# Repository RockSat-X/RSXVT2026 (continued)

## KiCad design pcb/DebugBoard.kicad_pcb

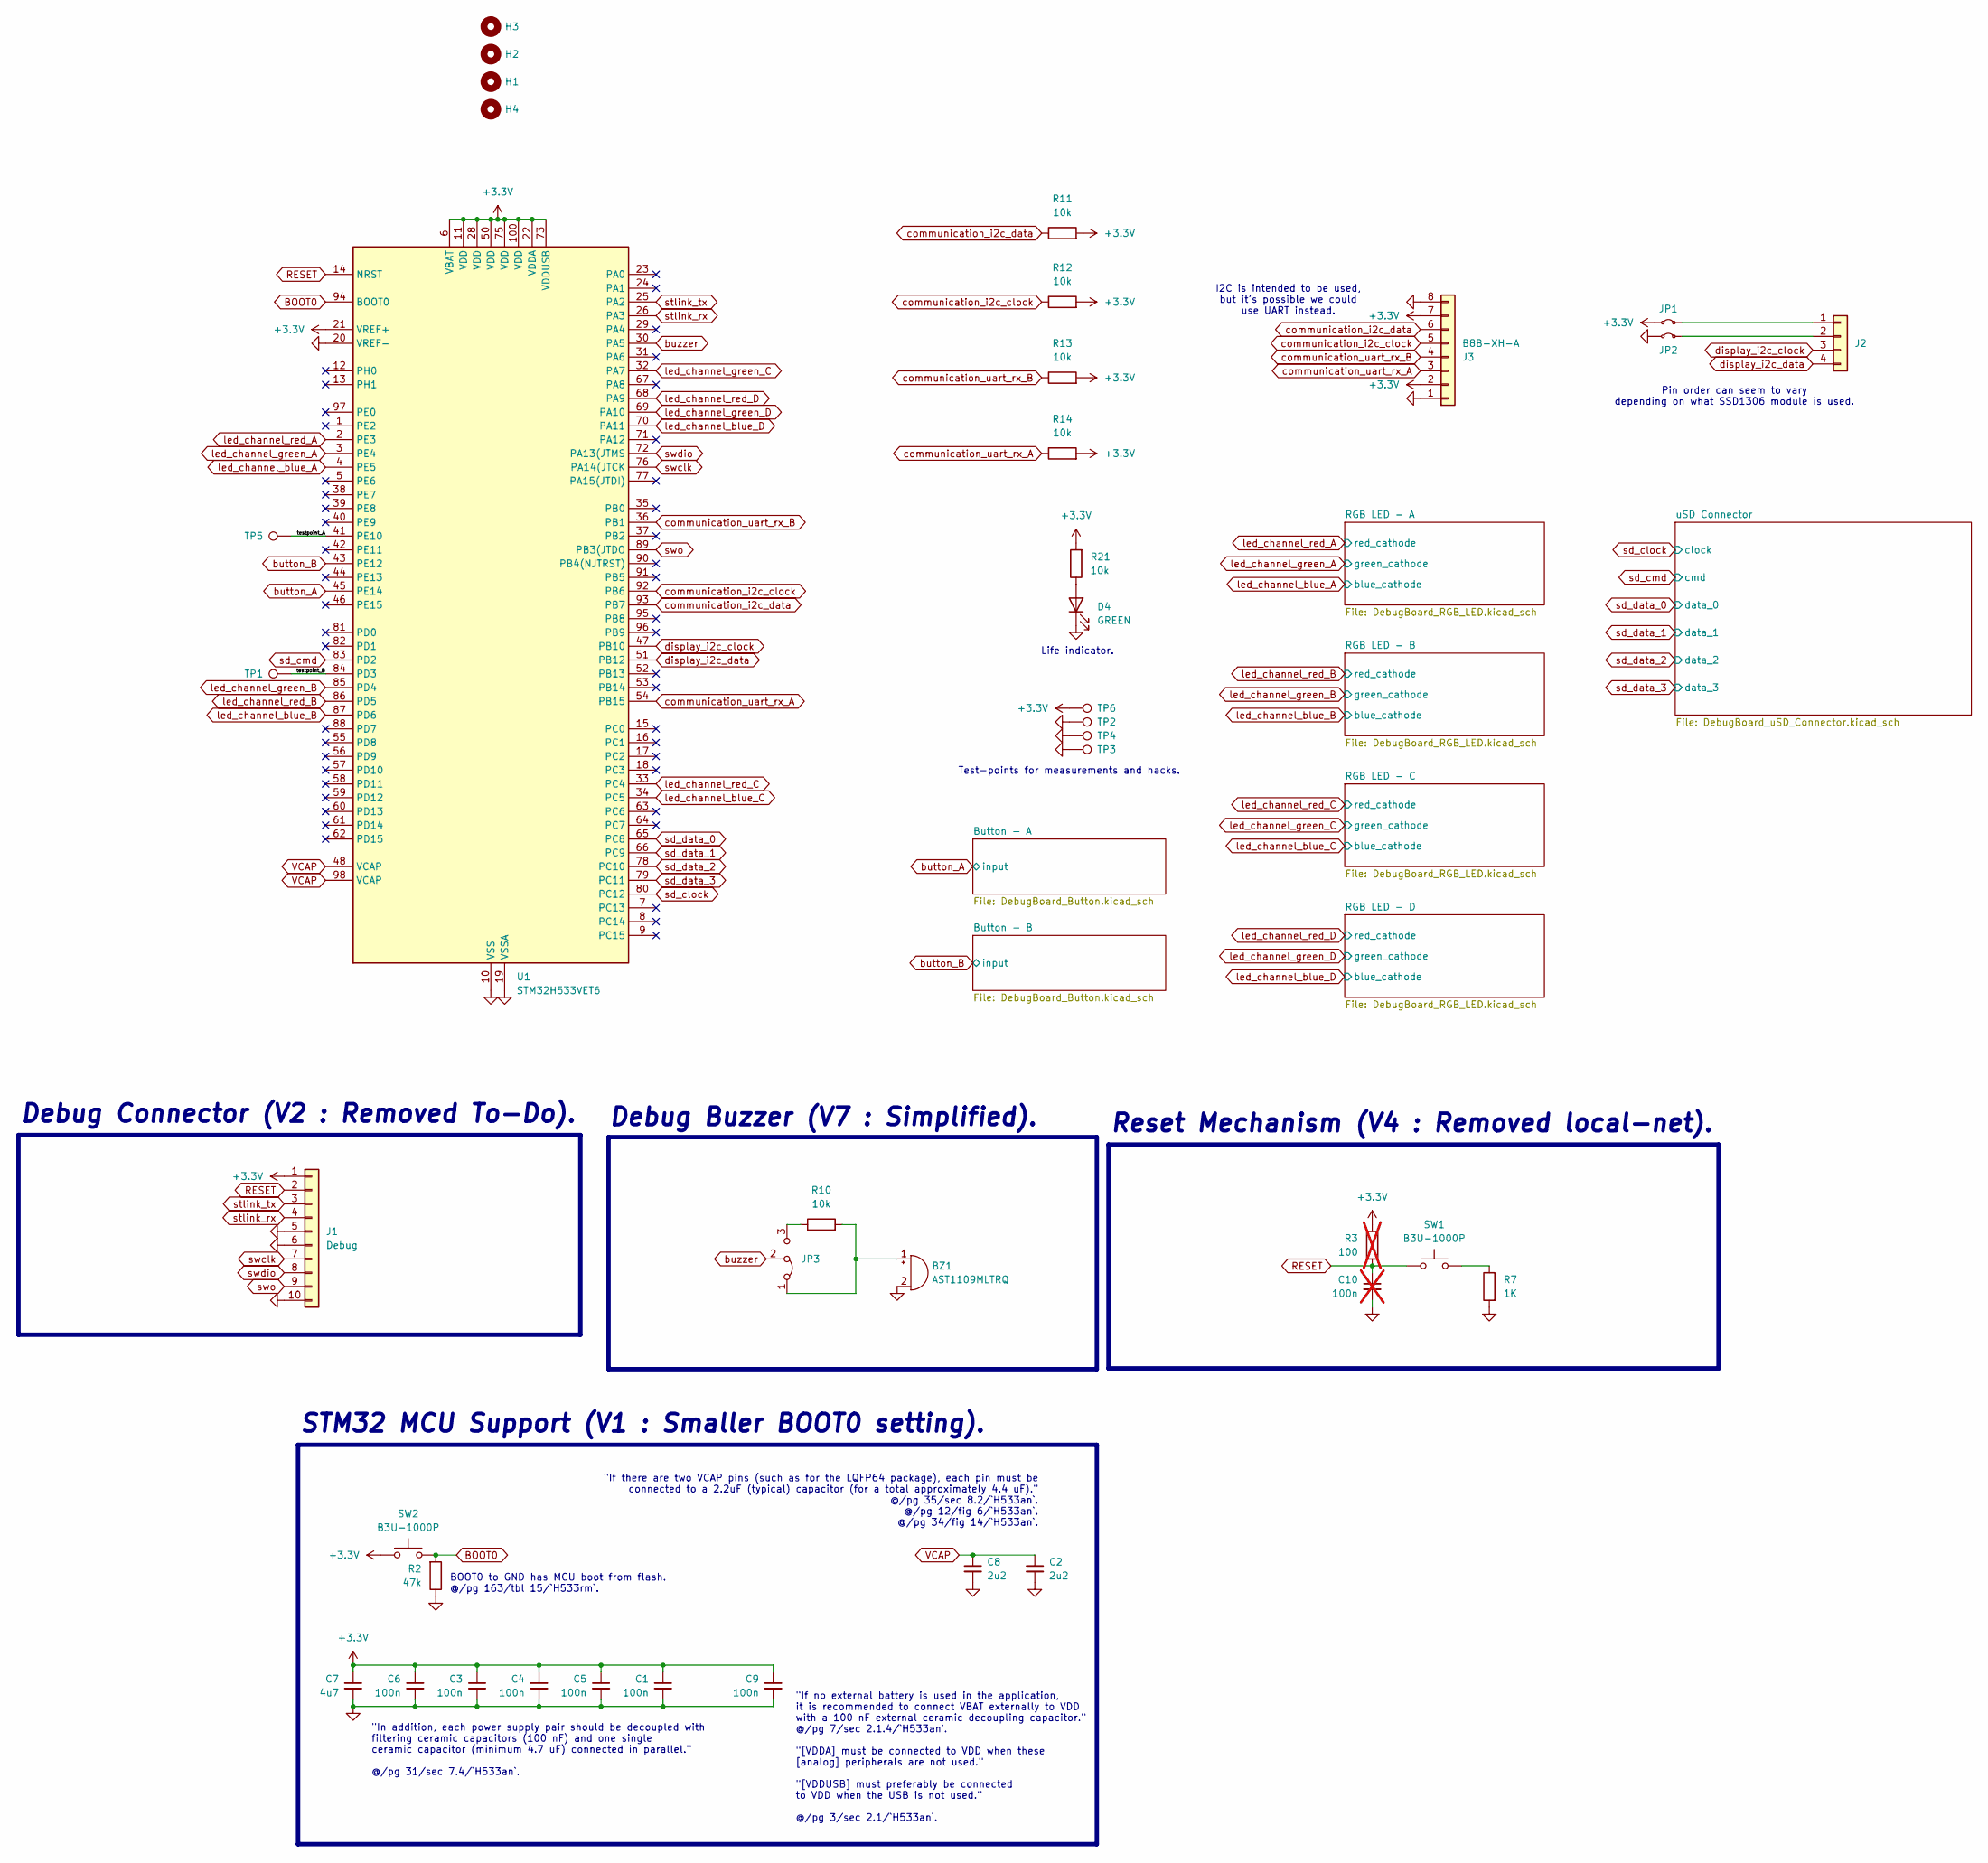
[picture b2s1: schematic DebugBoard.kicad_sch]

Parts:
BZ1: AST1109MLTRQ; Buzzer_Mallory_AST1109MLTRQ
C1, C3, C4, C5, C6, C9: 100n; C_1206_3216Metric_Pad1.33x1.80mm_HandSolder
C2, C8: 2u2; C_1206_3216Metric_Pad1.33x1.80mm_HandSolder
C7: 4u7; C_1206_3216Metric_Pad1.33x1.80mm_HandSolder
C10: 100n; C_1206_3216Metric_Pad1.33x1.80mm_HandSolder; not fitted
D4: GREEN; LED_1206_3216Metric_Pad1.42x1.75mm_HandSolder
H1, H2, H3, H4: MountingHole; MountingHole_3.2mm_M3
J1: Debug; Molex_PicoBlade_53047-1010_1x10_P1.25mm_Vertical
J2: Conn_01x04; SSD1306_Module_Connector
J3: B8B-XH-A; JST_XH_B8B-XH-A_1x08_P2.50mm_Vertical
JP1, JP2: Jumper_2_Small_Bridged; TestPoint_2Pads_Pitch2.54mm_Drill0.8mm
JP3: Jumper_3_Bridged12; PinHeader_1x03_P2.54mm_Vertical
R2: 47k; R_1206_3216Metric_Pad1.30x1.75mm_HandSolder
R3: 100; R_1206_3216Metric_Pad1.30x1.75mm_HandSolder; not fitted
R7: 1K; R_1206_3216Metric_Pad1.30x1.75mm_HandSolder
R10, R11, R12, R13, R14, R21: 10k; R_1206_3216Metric_Pad1.30x1.75mm_HandSolder
SW1, SW2: B3U-1000P; SW_SPST_B3U-1000P
TP1, TP2, TP3, TP4, TP5, TP6: TestPoint; TestPoint_Bridge_Pitch2.0mm_Drill0.7mm
U1: STM32H533VET6; LQFP-100_14x14mm_P0.5mm

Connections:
+3.3V: C1.1, C3.1, C4.1, C5.1, C6.1, C7.1, C9.1, J1.1, J3.2, J3.7, JP1.1 (A), R3.1, R11.2, R12.2, R13.2, R14.2, R21.2, SW2.1, TP6.1, U1.6 (VBAT), U1.11 (VDD), U1.21 (VREF+), U1.22 (VDDA), U1.28 (VDD), U1.50 (VDD), U1.73 (VDDUSB), U1.75 (VDD), U1.100 (VDD); also elsewhere on the board
/testpoint_A: TP5.1, U1.41 (PE10)
/testpoint_B: TP1.1, U1.84 (PD3)
BOOT0: R2.2, SW2.2, U1.94 (BOOT0)
GND: BZ1.2 (-), C1.2, C2.2, C3.2, C4.2, C5.2, C6.2, C7.2, C8.2, C9.2, C10.2, D4.1 (K), J1.5, J1.6, J1.10, J3.1, J3.8, JP2.1 (A), R2.1, R7.2, TP2.1, TP3.1, TP4.1, U1.10 (VSS), U1.19 (VSSA), U1.20 (VREF-), U1.27 (VSS), U1.49 (VSS), U1.74 (VSS), U1.99 (VSS); also elsewhere on the board
unnamed: BZ1.1 (+), JP3.1 (A), R10.2
unnamed: D4.2 (A), R21.1
unnamed: J2.1, JP1.2 (B)
unnamed: J2.2, JP2.2 (B)
unnamed: JP3.3 (B), R10.1
unnamed: R7.1, SW1.2
RESET: C10.1, J1.2, R3.2, SW1.1, U1.14 (NRST)
VCAP: C2.1, C8.1, U1.48 (VCAP), U1.98 (VCAP)
button_A: U1.45 (PE14); also elsewhere on the board
button_B: U1.43 (PE12); also elsewhere on the board
buzzer: JP3.2 (C), U1.30 (PA5)
communication_i2c_clock: J3.5, R12.1, U1.92 (PB6)
communication_i2c_data: J3.6, R11.1, U1.93 (PB7)
communication_uart_rx_A: J3.3, R14.1, U1.54 (PB15)
communication_uart_rx_B: J3.4, R13.1, U1.36 (PB1)
display_i2c_clock: J2.3, U1.47 (PB10)
display_i2c_data: J2.4, U1.51 (PB12)
led_channel_blue_A: U1.4 (PE5); also elsewhere on the board
led_channel_blue_B: U1.87 (PD6); also elsewhere on the board
led_channel_blue_C: U1.34 (PC5); also elsewhere on the board
led_channel_blue_D: U1.70 (PA11); also elsewhere on the board
led_channel_green_A: U1.3 (PE4); also elsewhere on the board
led_channel_green_B: U1.85 (PD4); also elsewhere on the board
led_channel_green_C: U1.32 (PA7); also elsewhere on the board
led_channel_green_D: U1.69 (PA10); also elsewhere on the board
led_channel_red_A: U1.2 (PE3); also elsewhere on the board
led_channel_red_B: U1.86 (PD5); also elsewhere on the board
led_channel_red_C: U1.33 (PC4); also elsewhere on the board
led_channel_red_D: U1.68 (PA9); also elsewhere on the board
sd_clock: U1.80 (PC12); also elsewhere on the board
sd_cmd: U1.83 (PD2); also elsewhere on the board
sd_data_0: U1.65 (PC8); also elsewhere on the board
sd_data_1: U1.66 (PC9); also elsewhere on the board
sd_data_2: U1.78 (PC10); also elsewhere on the board
sd_data_3: U1.79 (PC11); also elsewhere on the board
stlink_rx: J1.4, U1.26 (PA3)
stlink_tx: J1.3, U1.25 (PA2)
swclk: J1.7, U1.76 (PA14(JTCK)
swdio: J1.8, U1.72 (PA13(JTMS)
swo: J1.9, U1.89 (PB3(JTDO)

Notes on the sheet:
STM32 MCU Support (V1 : Smaller BOOT0 setting).
Pin order can seem to vary depending on what SSD1306 module is used.
I2C is intended to be used, but it's possible we could use UART instead.
Reset Mechanism (V4 : Removed local-net).
Debug Connector (V2 : Removed To-Do).
BOOT0 to GND has MCU boot from flash. @/pg 163/tbl 15/`H533rm`.
Life indicator.
Test-points for measurements and hacks.
"If there are two VCAP pins (such as for the LQFP64 package), each pin must be connected to a 2.2uF (typical) capacitor (for a total approximately 4.4 uF)." @/pg 35/sec 8.2/`H533an`. @/pg 12/fig 6/`H533an`. @/pg 34/fig 14/`H533an`.
"In addition, each power supply pair should be decoupled with filtering ceramic capacitors (100 nF) and one single ceramic capacitor (minimum 4.7 uF) connected in parallel." @/pg 31/sec 7.4/`H533an`.
"If no external battery is used in the application, it is recommended to connect VBAT externally to VDD with a 100 nF external ceramic decoupling capacitor." @/pg 7/sec 2.1.4/`H533an`. "[VDDA] must be connected to VDD when these [analog] peripherals are not used." "[VDDUSB] must preferably be conne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
Debug Buzzer (V7 : Simplified).

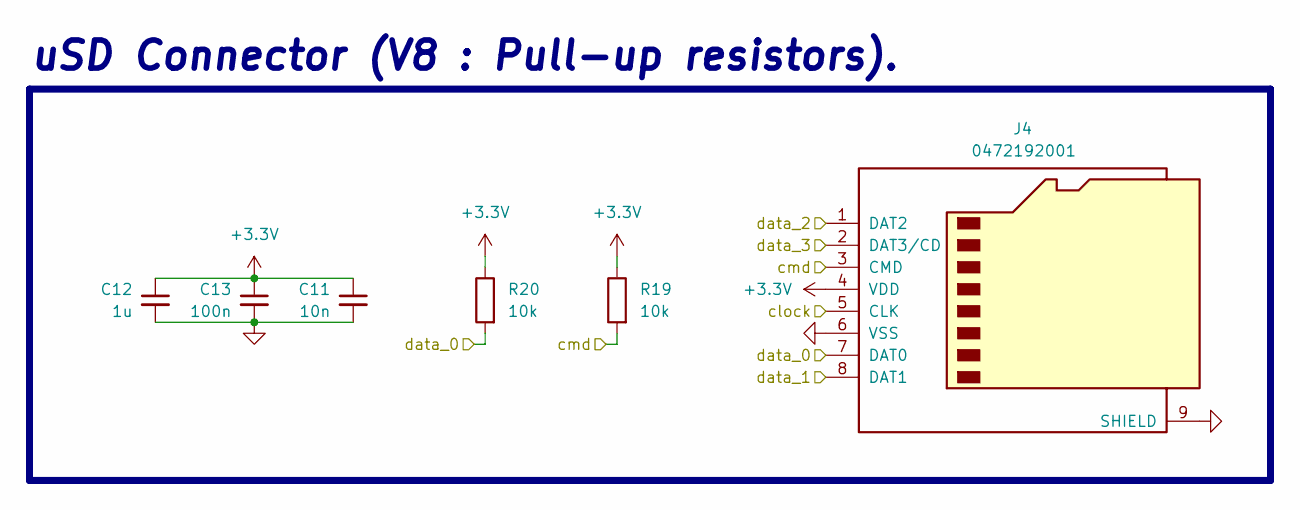
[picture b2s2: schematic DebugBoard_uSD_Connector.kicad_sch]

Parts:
C11: 10n; C_1206_3216Metric_Pad1.33x1.80mm_HandSolder
C12: 1u; C_1206_3216Metric_Pad1.33x1.80mm_HandSolder
C13: 100n; C_1206_3216Metric_Pad1.33x1.80mm_HandSolder
J4: 0472192001; microSD_HC_Molex_47219-2001
R19, R20: 10k; R_1206_3216Metric_Pad1.30x1.75mm_HandSolder

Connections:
+3.3V: C11.1, C12.1, C13.1, J4.4 (VDD), R19.1, R20.1; also elsewhere on the board
GND: C11.2, C12.2, C13.2, J4.6 (VSS), J4.9 (SHIELD); also elsewhere on the board
sd_clock: J4.5 (CLK); also elsewhere on the board
sd_cmd: J4.3 (CMD), R19.2; also elsewhere on the board
sd_data_0: J4.7 (DAT0), R20.2; also elsewhere on the board
sd_data_1: J4.8 (DAT1); also elsewhere on the board
sd_data_2: J4.1 (DAT2); also elsewhere on the board
sd_data_3: J4.2 (DAT3/CD); also elsewhere on the board

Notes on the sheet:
uSD Connector (V8 : Pull-up resistors).

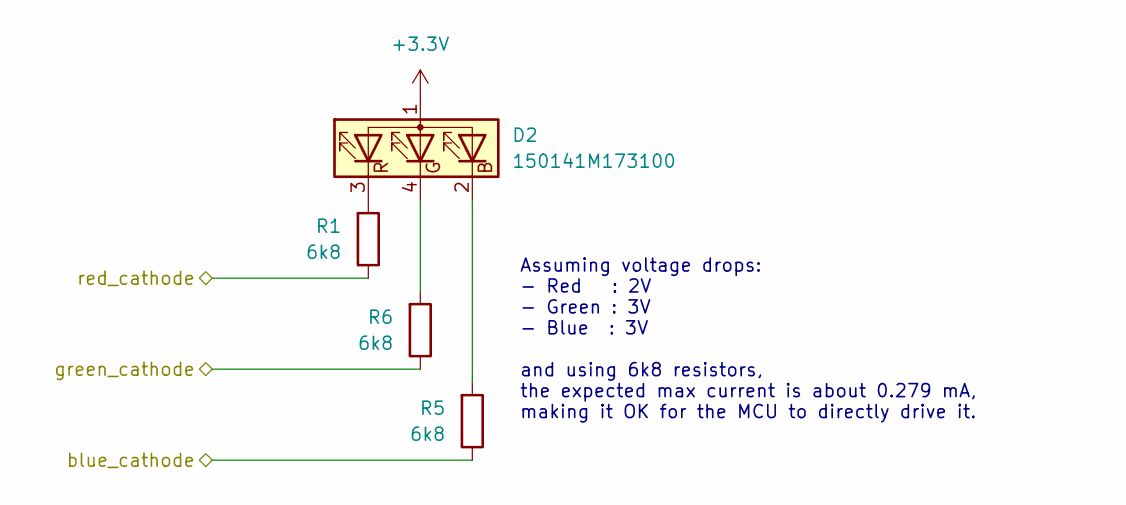
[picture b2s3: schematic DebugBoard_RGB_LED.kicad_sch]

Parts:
D2: 150141M173100; LED_RGB_Wuerth-PLCC4_3.2x2.8mm_150141M173100
R1, R5, R6: 6k8; R_1206_3216Metric_Pad1.30x1.75mm_HandSolder

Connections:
+3.3V: D2.1 (A); also elsewhere on the board
unnamed: D2.2 (BK), R5.2
unnamed: D2.4 (GK), R6.2
unnamed: D2.3 (RK), R1.2
led_channel_blue_A: R5.1; also elsewhere on the board
led_channel_green_A: R6.1; also elsewhere on the board
led_channel_red_A: R1.1; also elsewhere on the board

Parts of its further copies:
D1, D3, D5: 150141M173100; LED_RGB_Wuerth-PLCC4_3.2x2.8mm_150141M173100
R4, R8, R9, R17, R18, R22, R23, R24, R25: 6k8; R_1206_3216Metric_Pad1.30x1.75mm_HandSolder

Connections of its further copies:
+3.3V: D1.1 (A), D3.1 (A), D5.1 (A); also elsewhere on the board
unnamed: D1.2 (BK), R8.2
unnamed: D1.4 (GK), R9.2
unnamed: D1.3 (RK), R4.2
unnamed: D3.2 (BK), R22.2
unnamed: D3.4 (GK), R23.2
unnamed: D3.3 (RK), R25.2
unnamed: D5.2 (BK), R18.2
unnamed: D5.4 (GK), R17.2
unnamed: D5.3 (RK), R24.2
led_channel_blue_B: R8.1; also elsewhere on the board
led_channel_blue_C: R18.1; also elsewhere on the board
led_channel_blue_D: R22.1; also elsewhere on the board
led_channel_green_B: R9.1; also elsewhere on the board
led_channel_green_C: R17.1; also elsewhere on the board
led_channel_green_D: R23.1; also elsewhere on the board
led_channel_red_B: R4.1; also elsewhere on the board
led_channel_red_C: R24.1; also elsewhere on the board
led_channel_red_D: R25.1; also elsewhere on the board

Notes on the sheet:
Assuming voltage drops: - Red : 2V - Green : 3V - Blue : 3V and using 6k8 resistors, the expected max current is about 0.279 mA, making it OK for the MCU to directly drive it.

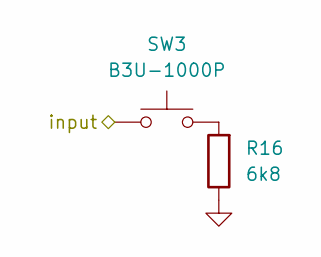
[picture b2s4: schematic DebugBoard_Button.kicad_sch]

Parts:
R16: 6k8; R_1206_3216Metric_Pad1.30x1.75mm_HandSolder
SW3: B3U-1000P; SW_SPST_B3U-1000P

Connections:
GND: R16.1; also elsewhere on the board
unnamed: R16.2, SW3.2
button_A: SW3.1; also elsewhere on the board

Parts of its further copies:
R15: 6k8; R_1206_3216Metric_Pad1.30x1.75mm_HandSolder
SW4: B3U-1000P; SW_SPST_B3U-1000P

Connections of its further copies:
GND: R15.1; also elsewhere on the board
unnamed: R15.2, SW4.2
button_B: SW4.1; also elsewhere on the board

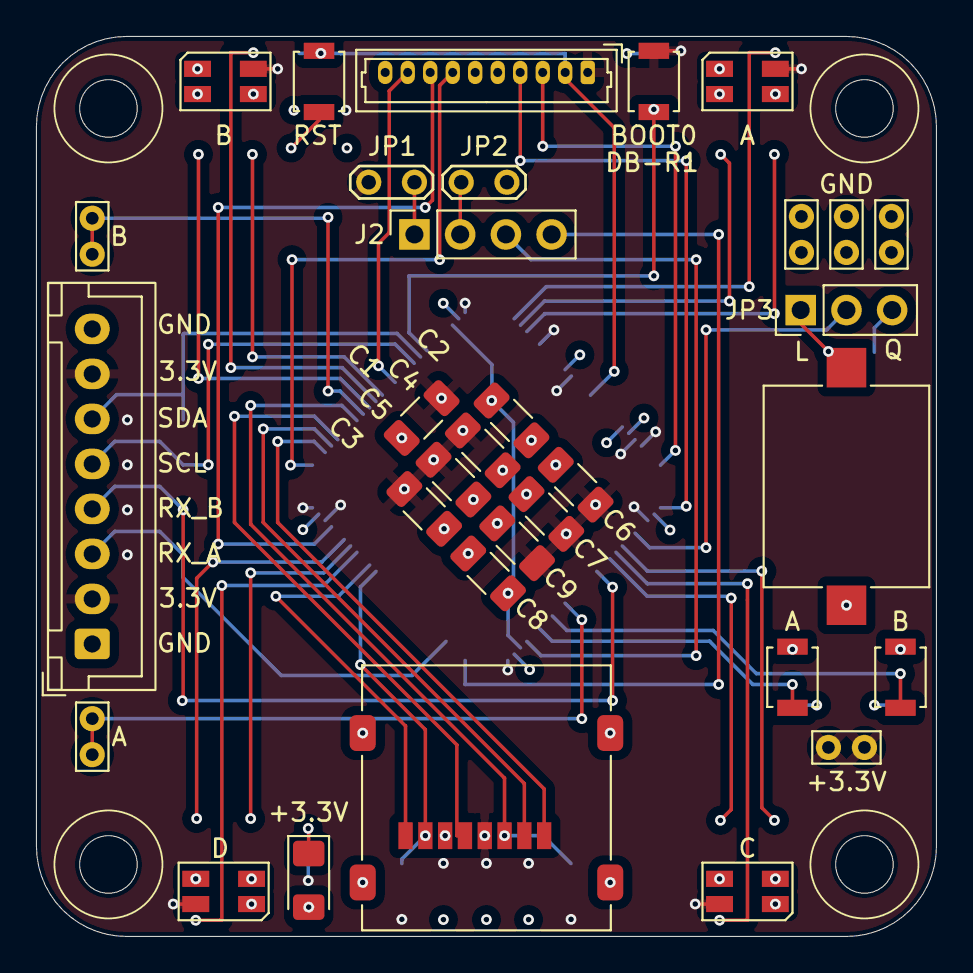
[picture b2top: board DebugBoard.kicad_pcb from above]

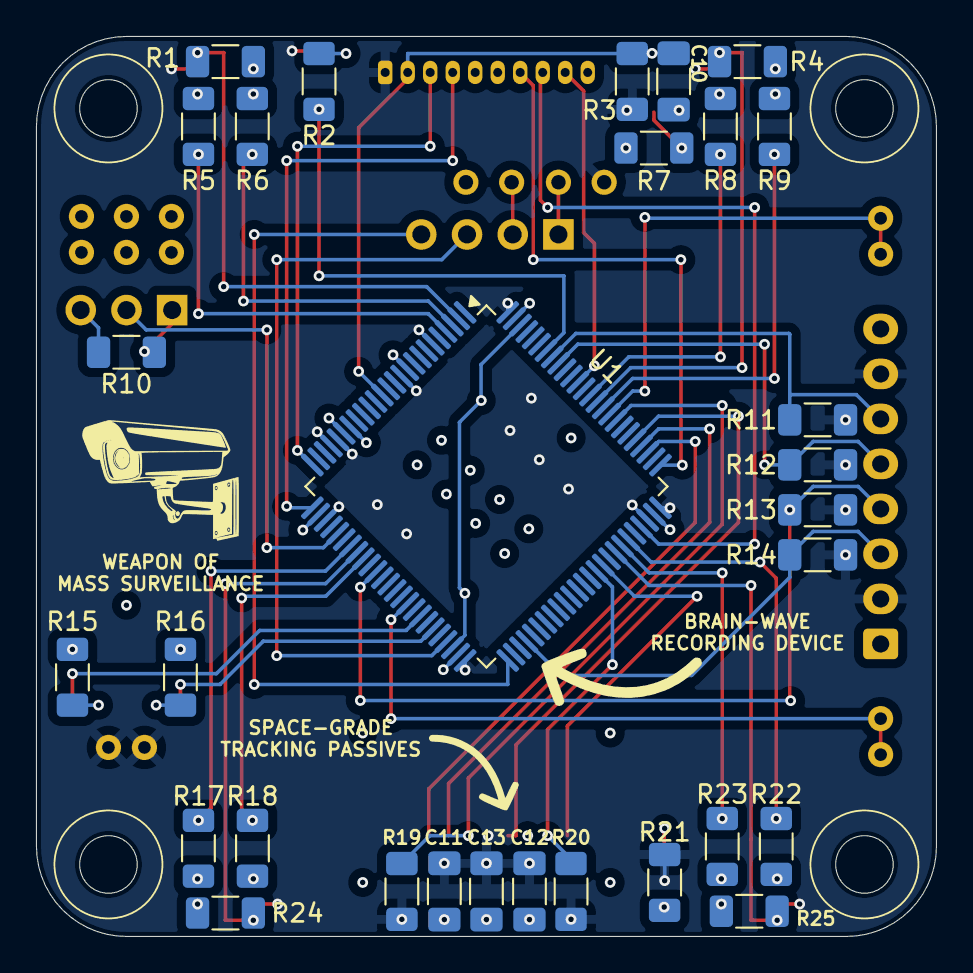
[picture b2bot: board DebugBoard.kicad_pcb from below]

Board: 4 copper layers, 50.0 x 50.0 mm, 66 parts (30 on the bottom side), 59 nets.

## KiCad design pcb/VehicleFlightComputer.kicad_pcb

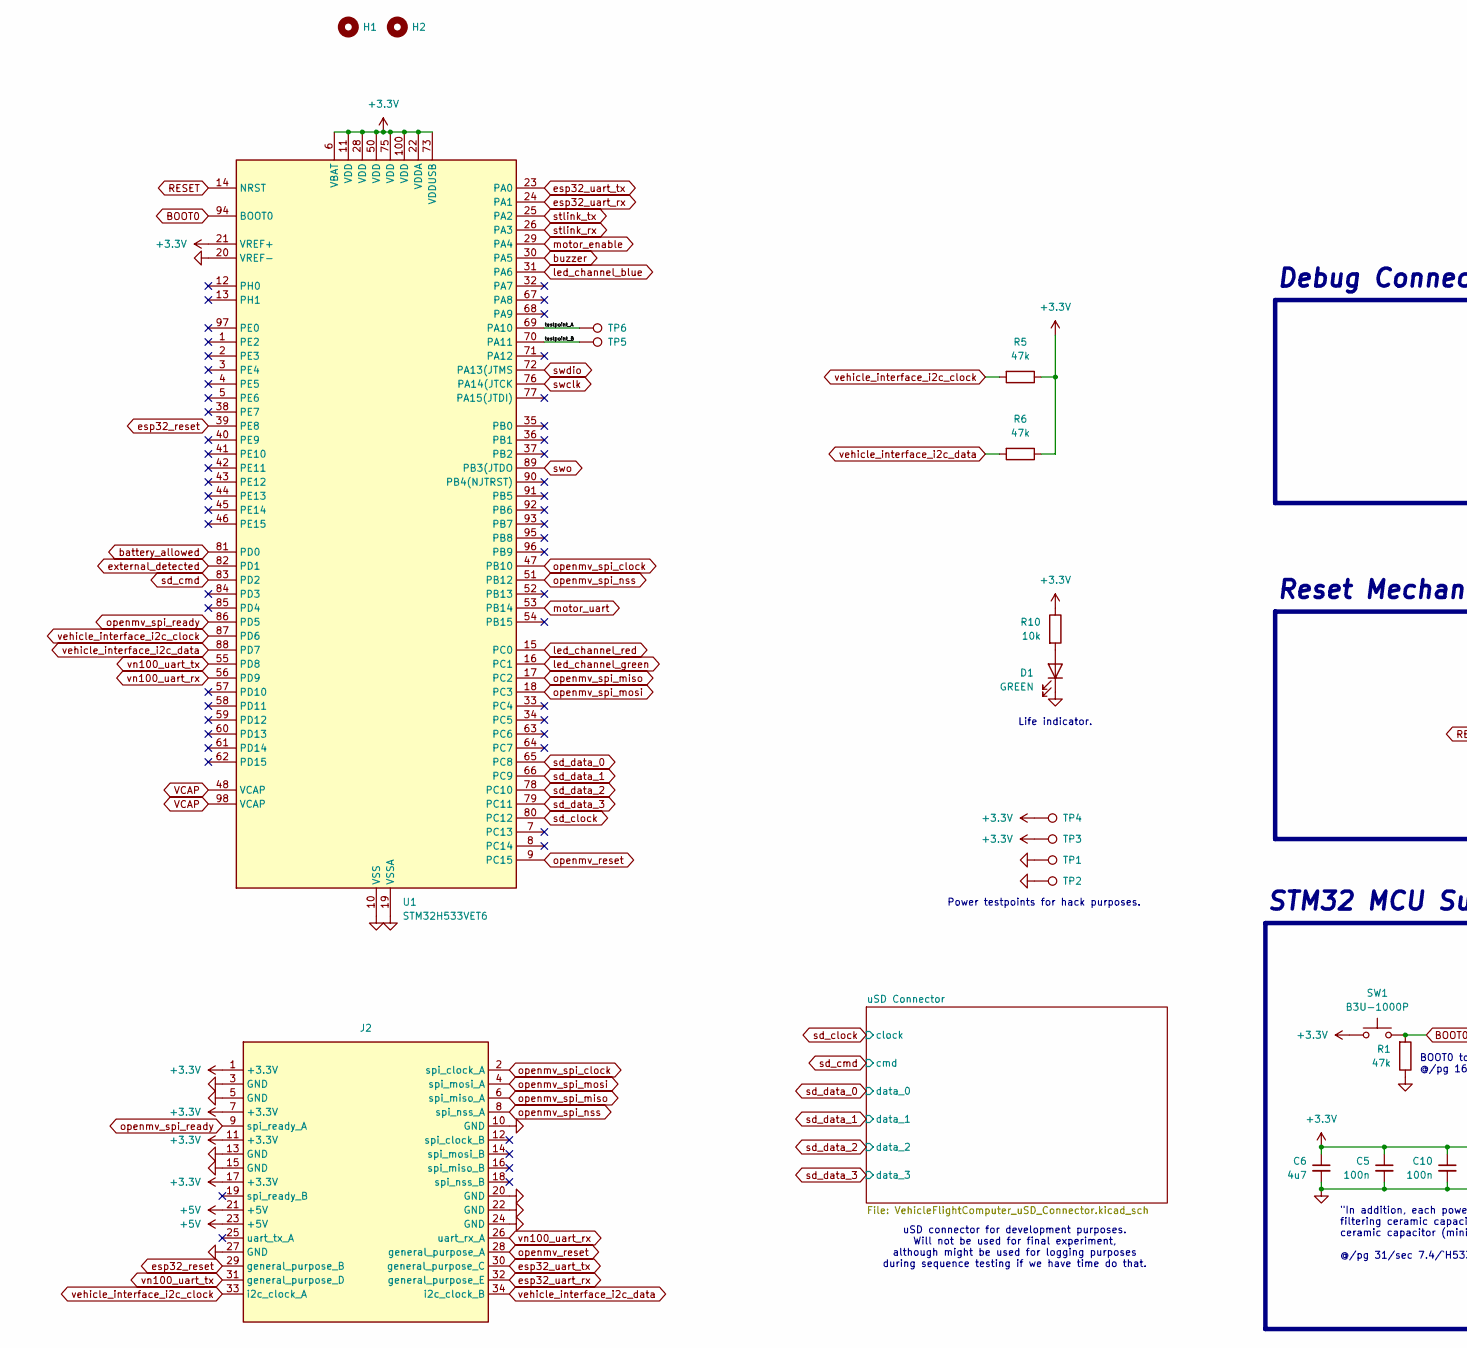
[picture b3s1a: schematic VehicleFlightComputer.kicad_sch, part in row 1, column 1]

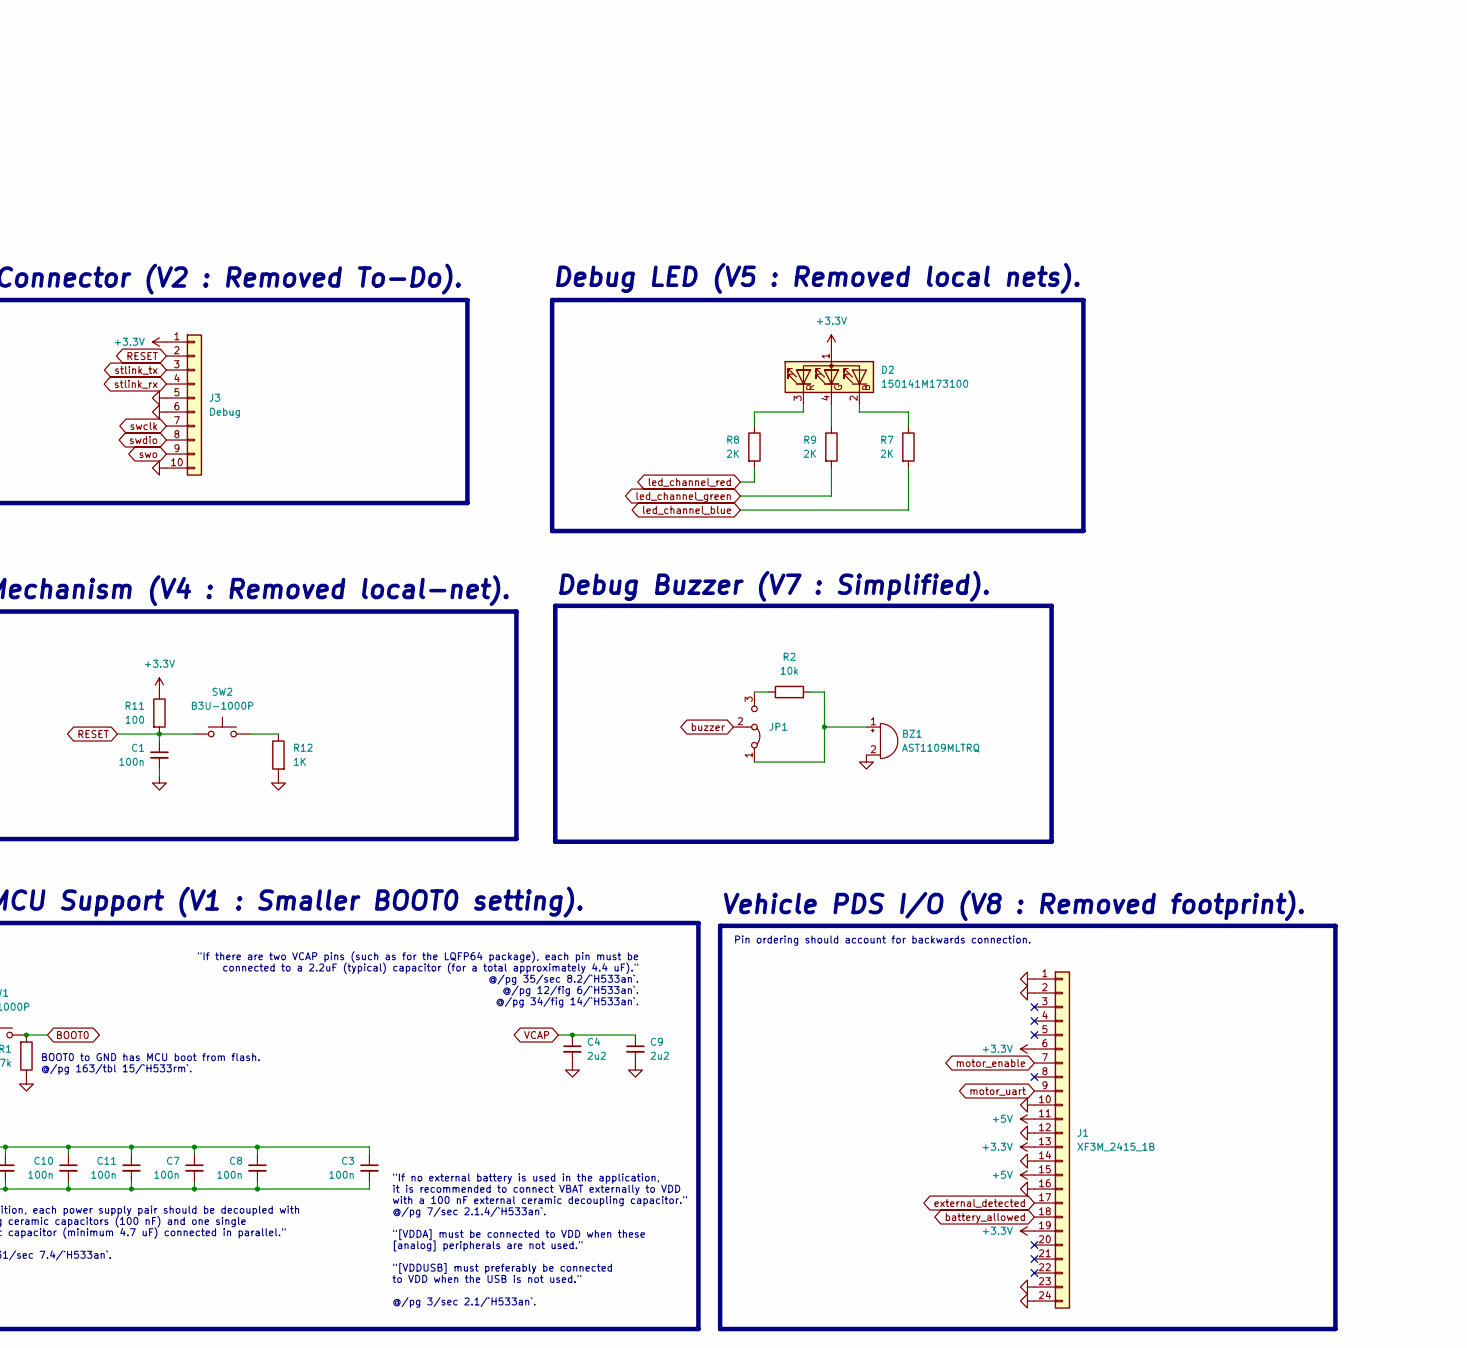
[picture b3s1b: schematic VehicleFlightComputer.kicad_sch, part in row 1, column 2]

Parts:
BZ1: AST1109MLTRQ; Buzzer_Mallory_AST1109MLTRQ
C1, C3, C5, C7, C8, C10, C11: 100n; C_1206_3216Metric_Pad1.33x1.80mm_HandSolder
C4, C9: 2u2; C_1206_3216Metric_Pad1.33x1.80mm_HandSolder
C6: 4u7; C_1206_3216Metric_Pad1.33x1.80mm_HandSolder
D1: GREEN; LED_1206_3216Metric_Pad1.42x1.75mm_HandSolder
D2: 150141M173100; LED_RGB_Wuerth-PLCC4_3.2x2.8mm_150141M173100
H1, H2: MountingHole; MountingHole_3.2mm_M3
J1: XF3M_2415_1B
J2: VehicleStackConnector
J3: Debug; Molex_PicoBlade_53047-1010_1x10_P1.25mm_Vertical
JP1: Jumper_3_Bridged12; PinHeader_1x03_P2.54mm_Vertical
R1, R5, R6: 47k; R_1206_3216Metric_Pad1.30x1.75mm_HandSolder
R2, R10: 10k; R_1206_3216Metric_Pad1.30x1.75mm_HandSolder
R7, R8, R9: 2K; R_1206_3216Metric_Pad1.30x1.75mm_HandSolder
R11: 100; R_1206_3216Metric_Pad1.30x1.75mm_HandSolder
R12: 1K; R_1206_3216Metric_Pad1.30x1.75mm_HandSolder
SW1, SW2: B3U-1000P; SW_SPST_B3U-1000P
TP1, TP2, TP3, TP4, TP5, TP6: TestPoint; TestPoint_Bridge_Pitch2.0mm_Drill0.7mm
U1: STM32H533VET6; LQFP-100_14x14mm_P0.5mm

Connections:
+3.3V: C3.1, C5.1, C6.1, C7.1, C8.1, C10.1, C11.1, D2.1 (A), J1.6, J1.13, J1.19, J2.1 (+3.3V), J2.7 (+3.3V), J2.11 (+3.3V), J2.17 (+3.3V), J3.1, R5.1, R6.1, R10.1, R11.1, SW1.1, TP3.1, TP4.1, U1.6 (VBAT), U1.11 (VDD), U1.21 (VREF+), U1.22 (VDDA), U1.28 (VDD), U1.50 (VDD), U1.73 (VDDUSB), U1.75 (VDD), U1.100 (VDD); also elsewhere on the board
+5V: J1.11, J1.15, J2.21 (+5V), J2.23 (+5V)
/testpoint_A: TP6.1, U1.69 (PA10)
/testpoint_B: TP5.1, U1.70 (PA11)
BOOT0: R1.2, SW1.2, U1.94 (BOOT0)
GND: BZ1.2 (-), C1.2, C3.2, C4.2, C5.2, C6.2, C7.2, C8.2, C9.2, C10.2, C11.2, D1.1 (K), J1.1, J1.2, J1.10, J1.12, J1.14, J1.16, J1.23, J1.24, J2.3 (GND), J2.5 (GND), J2.10 (GND), J2.13 (GND), J2.15 (GND), J2.20 (GND), J2.22 (GND), J2.24 (GND), J2.27 (GND), J3.5, J3.6, J3.10, R1.1, R12.2, TP1.1, TP2.1, U1.10 (VSS), U1.19 (VSSA), U1.20 (VREF-), U1.27 (VSS), U1.49 (VSS), U1.74 (VSS), U1.99 (VSS); also elsewhere on the board
unnamed: BZ1.1 (+), JP1.1 (A), R2.2
unnamed: D1.2 (A), R10.2
unnamed: D2.2 (BK), R7.1
unnamed: D2.4 (GK), R9.1
unnamed: D2.3 (RK), R8.1
unnamed: JP1.3 (B), R2.1
unnamed: R12.1, SW2.2
RESET: C1.1, J3.2, R11.2, SW2.1, U1.14 (NRST)
VCAP: C4.1, C9.1, U1.48 (VCAP), U1.98 (VCAP)
battery_allowed: J1.18, U1.81 (PD0)
buzzer: JP1.2 (C), U1.30 (PA5)
esp32_reset: J2.29 (general_purpose_B), U1.39 (PE8)
esp32_uart_rx: J2.32 (general_purpose_E), U1.24 (PA1)
esp32_uart_tx: J2.30 (general_purpose_C), U1.23 (PA0)
external_detected: J1.17, U1.82 (PD1)
led_channel_blue: R7.2, U1.31 (PA6)
led_channel_green: R9.2, U1.16 (PC1)
led_channel_red: R8.2, U1.15 (PC0)
motor_enable: J1.7, U1.29 (PA4)
motor_uart: J1.9, U1.53 (PB14)
openmv_reset: J2.28 (general_purpose_A), U1.9 (PC15)
openmv_spi_clock: J2.2 (spi_clock_A), U1.47 (PB10)
openmv_spi_miso: J2.6 (spi_miso_A), U1.17 (PC2)
openmv_spi_mosi: J2.4 (spi_mosi_A), U1.18 (PC3)
openmv_spi_nss: J2.8 (spi_nss_A), U1.51 (PB12)
openmv_spi_ready: J2.9 (spi_ready_A), U1.86 (PD5)
sd_clock: U1.80 (PC12); also elsewhere on the board
sd_cmd: U1.83 (PD2); also elsewhere on the board
sd_data_0: U1.65 (PC8); also elsewhere on the board
sd_data_1: U1.66 (PC9); also elsewhere on the board
sd_data_2: U1.78 (PC10); also elsewhere on the board
sd_data_3: U1.79 (PC11); also elsewhere on the board
stlink_rx: J3.4, U1.26 (PA3)
stlink_tx: J3.3, U1.25 (PA2)
swclk: J3.7, U1.76 (PA14(JTCK)
swdio: J3.8, U1.72 (PA13(JTMS)
swo: J3.9, U1.89 (PB3(JTDO)
vehicle_interface_i2c_clock: J2.33 (i2c_clock_A), R5.2, U1.87 (PD6)
vehicle_interface_i2c_data: J2.34 (i2c_clock_B), R6.2, U1.88 (PD7)
vn100_uart_rx: J2.26 (uart_rx_A), U1.56 (PD9)
vn100_uart_tx: J2.31 (general_purpose_D), U1.55 (PD8)

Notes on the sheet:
Pin ordering should account for backwards connection.
STM32 MCU Support (V1 : Smaller BOOT0 setting).
Life indicator.
Reset Mechanism (V4 : Removed local-net).
Debug Connector (V2 : Removed To-Do).
BOOT0 to GND has MCU boot from flash. @/pg 163/tbl 15/`H533rm`.
uSD connector for development purposes. Will not be used for final experiment, although might be used for logging purposes during sequence testing if we have time do that.
"If there are two VCAP pins (such as for the LQFP64 package), each pin must be connected to a 2.2uF (typical) capacitor (for a total approximately 4.4 uF)." @/pg 35/sec 8.2/`H533an`. @/pg 12/fig 6/`H533an`. @/pg 34/fig 14/`H533an`.
Vehicle PDS I/O (V8 : Removed footprint).
Power testpoints for hack purposes.
"In addition, each power supply pair should be decoupled with filtering ceramic capacitors (100 nF) and one single ceramic capacitor (minimum 4.7 uF) connected in parallel." @/pg 31/sec 7.4/`H533an`.
"If no external battery is used in the application, it is recommended to connect VBAT externally to VDD with a 100 nF external ceramic decoupling capacitor." @/pg 7/sec 2.1.4/`H533an`. "[VDDA] must be connected to VDD when these [analog] peripherals are not used." "[VDDUSB] must preferably be conne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
Debug Buzzer (V7 : Simplified).
Debug LED (V5 : Removed local nets).

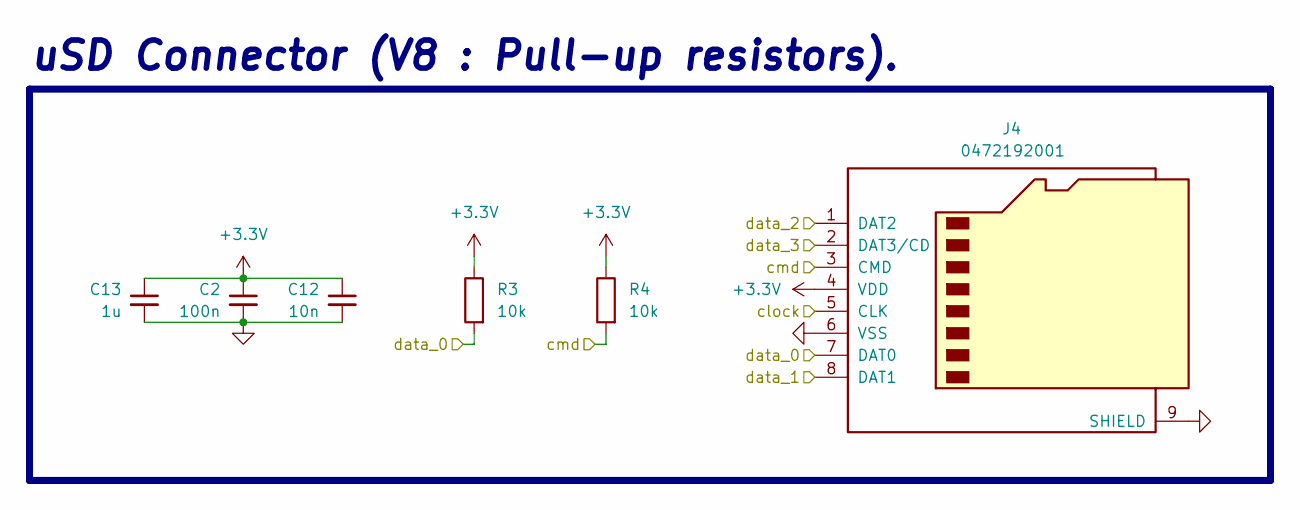
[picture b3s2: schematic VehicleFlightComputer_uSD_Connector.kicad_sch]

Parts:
C2: 100n; C_1206_3216Metric_Pad1.33x1.80mm_HandSolder
C12: 10n; C_1206_3216Metric_Pad1.33x1.80mm_HandSolder
C13: 1u; C_1206_3216Metric_Pad1.33x1.80mm_HandSolder
J4: 0472192001; microSD_HC_Molex_47219-2001
R3, R4: 10k; R_1206_3216Metric_Pad1.30x1.75mm_HandSolder

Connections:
+3.3V: C2.1, C12.1, C13.1, J4.4 (VDD), R3.1, R4.1; also elsewhere on the board
GND: C2.2, C12.2, C13.2, J4.6 (VSS), J4.9 (SHIELD); also elsewhere on the board
sd_clock: J4.5 (CLK); also elsewhere on the board
sd_cmd: J4.3 (CMD), R4.2; also elsewhere on the board
sd_data_0: J4.7 (DAT0), R3.2; also elsewhere on the board
sd_data_1: J4.8 (DAT1); also elsewhere on the board
sd_data_2: J4.1 (DAT2); also elsewhere on the board
sd_data_3: J4.2 (DAT3/CD); also elsewhere on the board

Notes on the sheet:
uSD Connector (V8 : Pull-up resistors).

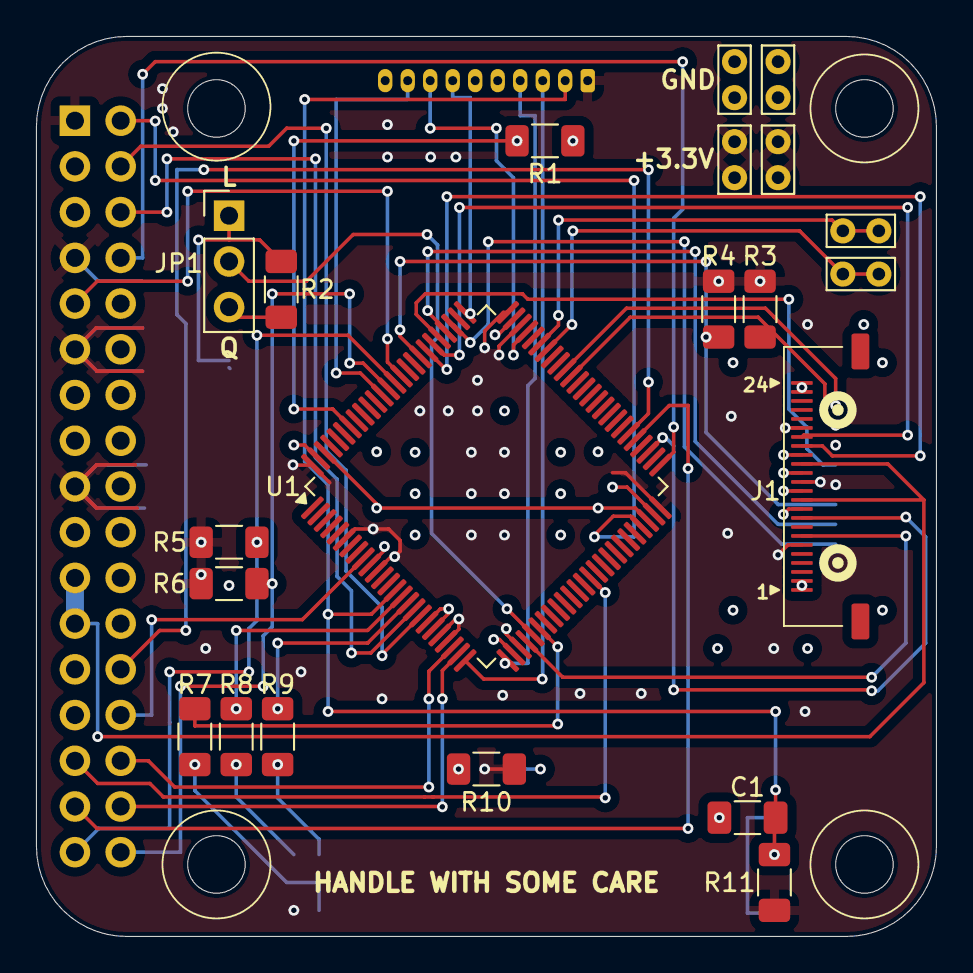
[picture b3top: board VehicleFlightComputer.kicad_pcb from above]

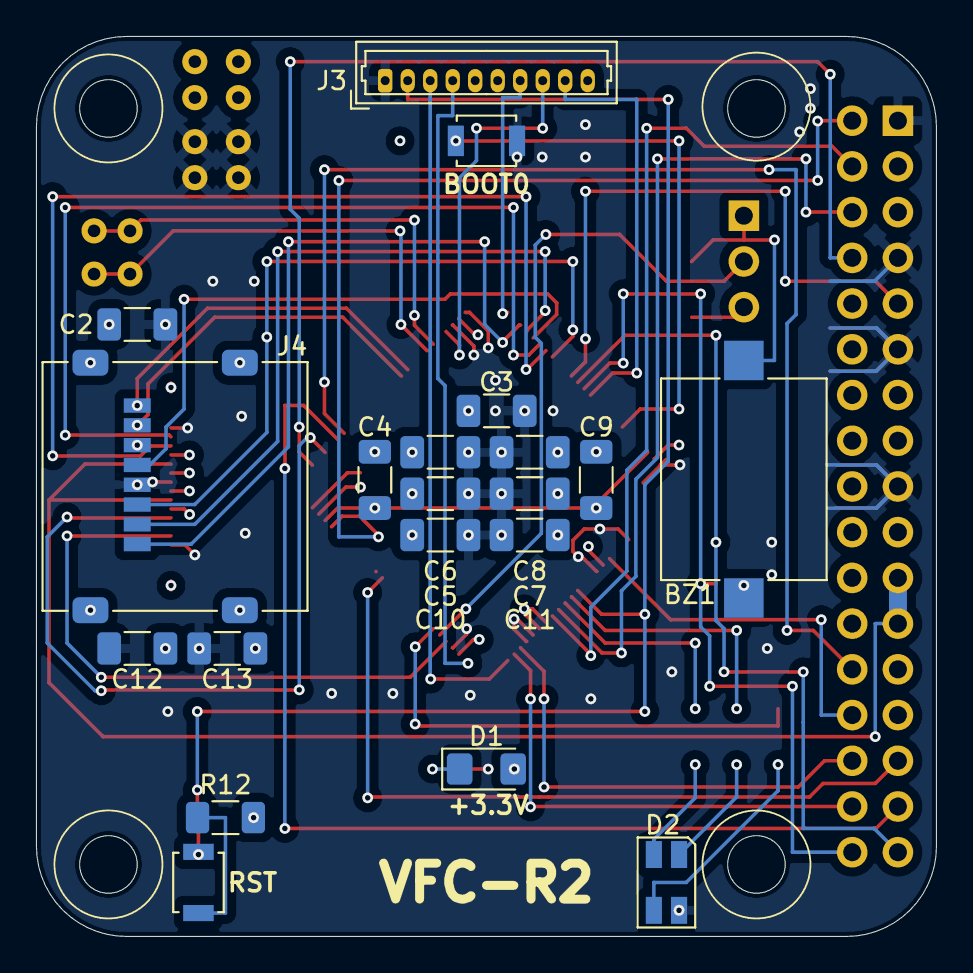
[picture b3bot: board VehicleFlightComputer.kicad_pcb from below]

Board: 4 copper layers, 50.0 x 50.0 mm, 45 parts (20 on the bottom side), 47 nets.

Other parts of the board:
N1: Housing; VehicleFlightComputerHousing
